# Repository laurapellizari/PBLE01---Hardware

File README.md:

# PBLE01---Hardware
Embedded hardware design for learning

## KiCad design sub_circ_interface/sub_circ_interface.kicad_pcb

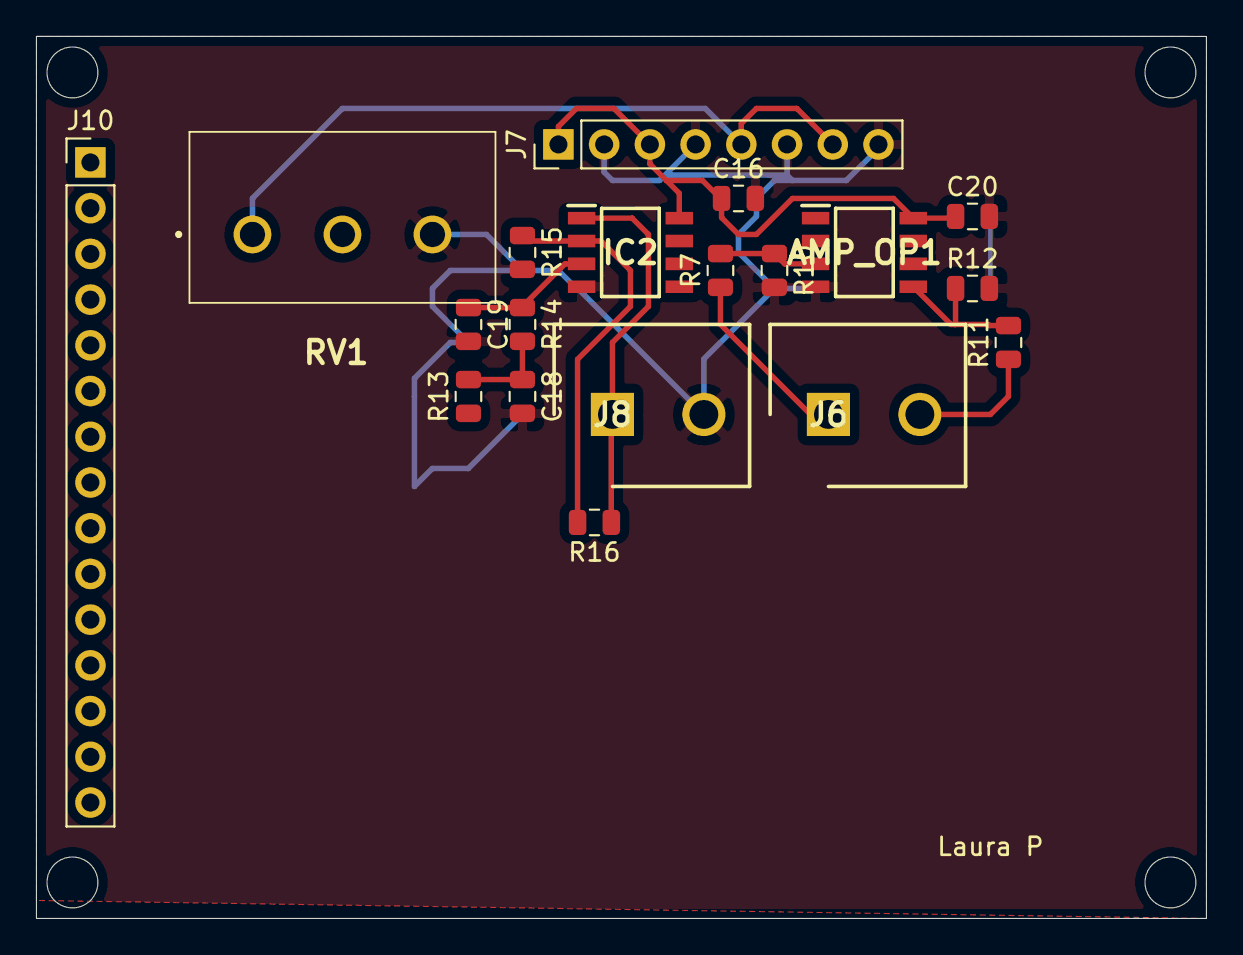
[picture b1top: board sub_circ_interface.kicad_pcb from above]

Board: 2 copper layers, 65.0 x 49.0 mm, 19 parts (0 on the bottom side), 11 nets.

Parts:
AMP_OP1: LM358DG; SOIC127P600X175-8N
C16, C20: 100nF; C_0805_2012Metric
C18, C19: 220nF; C_0805_2012Metric
IC2: LM358DG; SOIC127P600X175-8N
J6, J8: OSTTA024163; SHDR2W100P0X508_1X2_1086X900X1300P
J7: ALIM; PinHeader_1x08_P2.54mm_Vertical
J10: EXTENSÃO; PinHeader_1x15_P2.54mm_Vertical
R7, R11: 4k3; R_0805_2012Metric
R10, R12: 8k2; R_0805_2012Metric
R13: 1k; R_0805_2012Metric
R14: 3k3; R_0805_2012Metric
R15: 10k; R_0805_2012Metric
R16: 5k1; R_0805_2012Metric
RV1: POT; P160KN0QD15B10K

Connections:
+3V3: J7.5, J7.7, RV1.1
+5V: AMP_OP1.8, C16.1, C20.1, IC2.8, J7.1, J7.3
Earth: AMP_OP1.4, C16.2, C18.2, C19.2, C20.2, IC2.4, J7.2, J7.4, J7.6, J7.8, J8.2, R10.2, R12.2, R15.2, RV1.3
IN_A: AMP_OP1.3, R7.2, R10.1
IN_B: AMP_OP1.5, R11.2, R12.1
unnamed: C18.1, R13.2, R14.2
unnamed: C19.1, IC2.3, R14.1
unnamed: IC2.1, J8.1, R16.1
unnamed: IC2.2, R15.1, R16.2
unnamed: J6.1, R7.1
unnamed: J6.2, R11.1

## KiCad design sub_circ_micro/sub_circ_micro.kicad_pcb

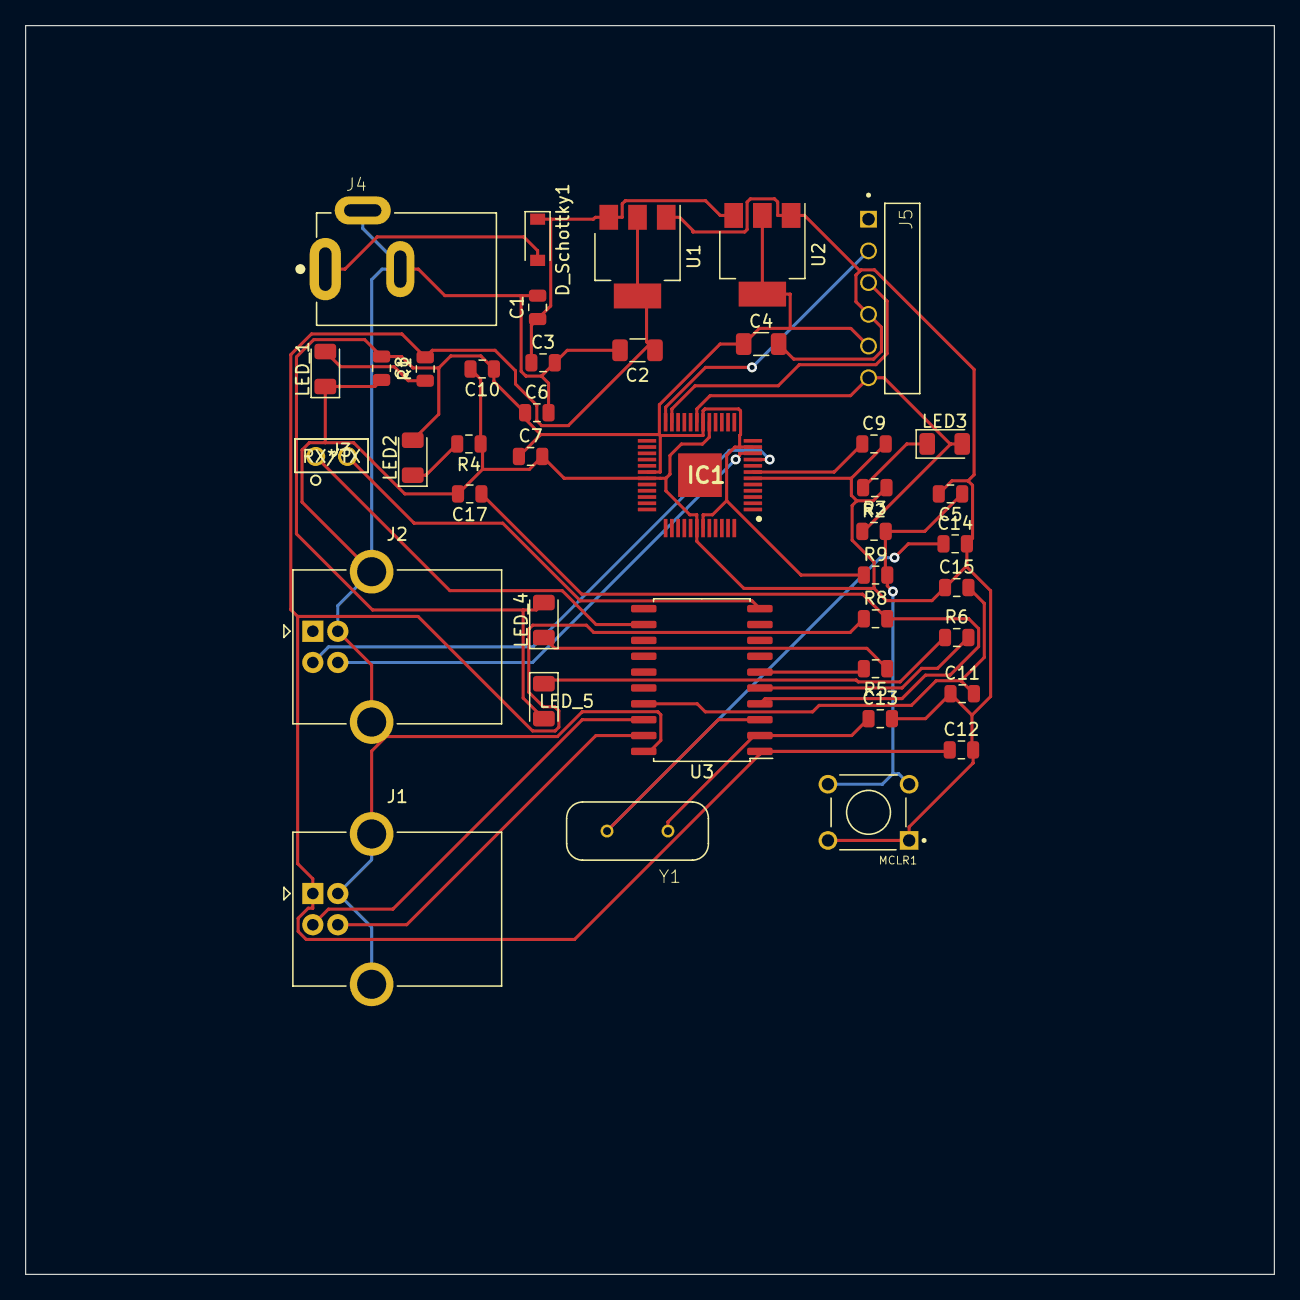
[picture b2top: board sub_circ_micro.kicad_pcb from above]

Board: 2 copper layers, 100.0 x 100.0 mm, 41 parts (0 on the bottom side), 27 nets.

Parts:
C1, C3, C5, C6, C7, C8, C10, C11, C12, C15, C17: 100nF; C_0805_2012Metric
C2, C4: 10uF; C_1206_3216Metric
C9: 10uF; C_0805_2012Metric
C13, C14: 22pF; C_0805_2012Metric
D_Schottky1: 1N5819; D_SOD-123
IC1: PIC32MM0064GPM048-I_PT; QFP50P900X900X120-49N
J1, J2: USB_B; USB_B_OST_USB-B1HSxx_Horizontal
J3: RX/TX; SSQ-102-03-T-S
J4: PJ-002A; CUI_PJ-002A
J5: ICSP; TE_826951-6
LED2: LED]; LED_1206_3216Metric
LED3: LED; LED_1206_3216Metric
LED_1: LED_ALIM; LED_1206_3216Metric
LED_4: Lx_LED; LED_1206_3216Metric
LED_5: Rx_LED; LED_1206_3216Metric
MCLR1: SWL1; SW_1825910-6-4
R1: 470; R_0805_2012Metric
R2: 1k; R_0805_2012Metric
R3, R4, R5, R6: 120; R_0805_2012Metric
R8: 4k7; R_0805_2012Metric
R9: 10k; R_0805_2012Metric
U1: LD1117S50TR_SOT223; SOT-223-3_TabPin2
U2: LD1117S33TR_SOT223; SOT-223-3_TabPin2
U3: MCP2200-I-SO; SOIC-20W_7.5x12.8mm_P1.27mm
Y1: 12MHz; XTAL_ECS-120-20-4X

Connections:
D+: J1.3, U3.19
D-: J1.2, U3.18
Earth: C1.2, C2.2, C3.2, C4.2, C5.2, C6.2, C7.2, C8.2, C9.2, C10.2, C11.1, C12.2, C13.2, C14.2, C15.1, C17.2, IC1.6, IC1.17, IC1.31, IC1.42, J1.4, J1.5, J2.4, J2.5, J4.2, J4.3, J5.4, LED_1.1, MCLR1.1, MCLR1.2, R3.1, R4.1, U1.1, U2.1, U3.20
MCLR#: IC1.19, J5.6, LED3.2, R2.1
unnamed: C5.1, MCLR1.3, MCLR1.4, R2.2, R9.2
unnamed: C11.2, C15.2, U3.17
unnamed: D_Schottky1.2, J4.1
unnamed: LED2.1, R4.2
unnamed: LED3.1, R3.2
unnamed: LED_1.2, R1.1
unnamed: LED_4.1, R5.1
unnamed: LED_5.1, R6.1
OSC1: C13.1, U3.2, Y1.1
OSC2: C14.1, U3.3, Y1.2
PGEC1: IC1.24, J5.2
PGED1: IC1.23, J5.3
RB10: IC1.9, J2.2
RB11: IC1.10, J2.3
RST: C17.1, R8.2, U3.4
RX: J3.1, U3.12
RxLED: R5.2, U3.6
TX: J3.2, U3.10
TxLED: R6.2, U3.5
VBUS: C2.1, C12.1, J1.1, R1.2, R8.1, U1.2, U3.1
VCAP: C9.1, IC1.7
VUSB3V3: C4.1, C6.1, C7.1, C8.1, C10.1, IC1.11, IC1.18, IC1.30, IC1.43, J5.5, LED2.2, LED_4.2, LED_5.2, R9.1, U2.2
Vin: C1.1, C3.1, D_Schottky1.1, U1.3, U2.3

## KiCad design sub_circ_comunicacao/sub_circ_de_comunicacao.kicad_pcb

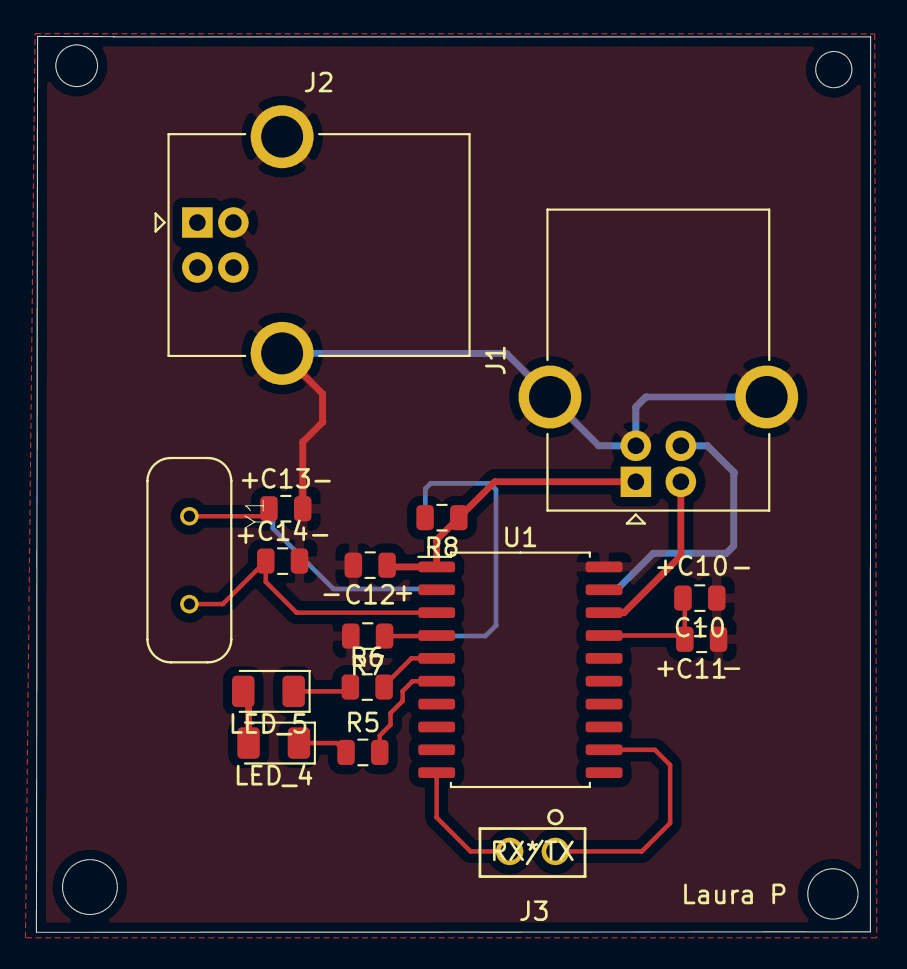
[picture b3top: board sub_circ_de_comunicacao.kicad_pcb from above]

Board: 2 copper layers, 46.3 x 49.8 mm, 16 parts (0 on the bottom side), 15 nets.

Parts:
C10, C11, C12: 100nF; C_0805_2012Metric
C13, C14: 22pF; C_0805_2012Metric
J1, J2: USB_B; USB_B_OST_USB-B1HSxx_Horizontal
J3: RX/TX; SSQ-102-03-T-S
LED_4: Lx_LED; LED_1206_3216Metric
LED_5: Rx_LED; LED_1206_3216Metric
R5, R6: 120; R_0805_2012Metric
R7: 10k; R_0805_2012Metric
R8: 4k7; R_0805_2012Metric
U1: MCP2200-I-SO; SOIC-20W_7.5x12.8mm_P1.27mm
Y1: 12MHz; XTAL_ECS-120-20-4X

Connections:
+3V3: LED_4.2, LED_5.2
D+: J1.3, U1.19
D-: J1.2, U1.18
Earth: C10.1, C11.1, C12.2, C13.2, C14.2, J1.4, J1.5, J2.4, J2.5, R7.2, U1.20
unnamed: C10.2, C11.2, U1.17
unnamed: LED_4.1, R5.1
unnamed: LED_5.1, R6.1
OSC1: C13.1, U1.2, Y1.1
OSC2: C14.1, U1.3, Y1.2
RST: R7.1, R8.2, U1.4
RX: J3.1, U1.12
RxLED: R5.2, U1.6
TX: J3.2, U1.10
TxLED: R6.2, U1.5
VBUS: C12.1, J1.1, R8.1, U1.1

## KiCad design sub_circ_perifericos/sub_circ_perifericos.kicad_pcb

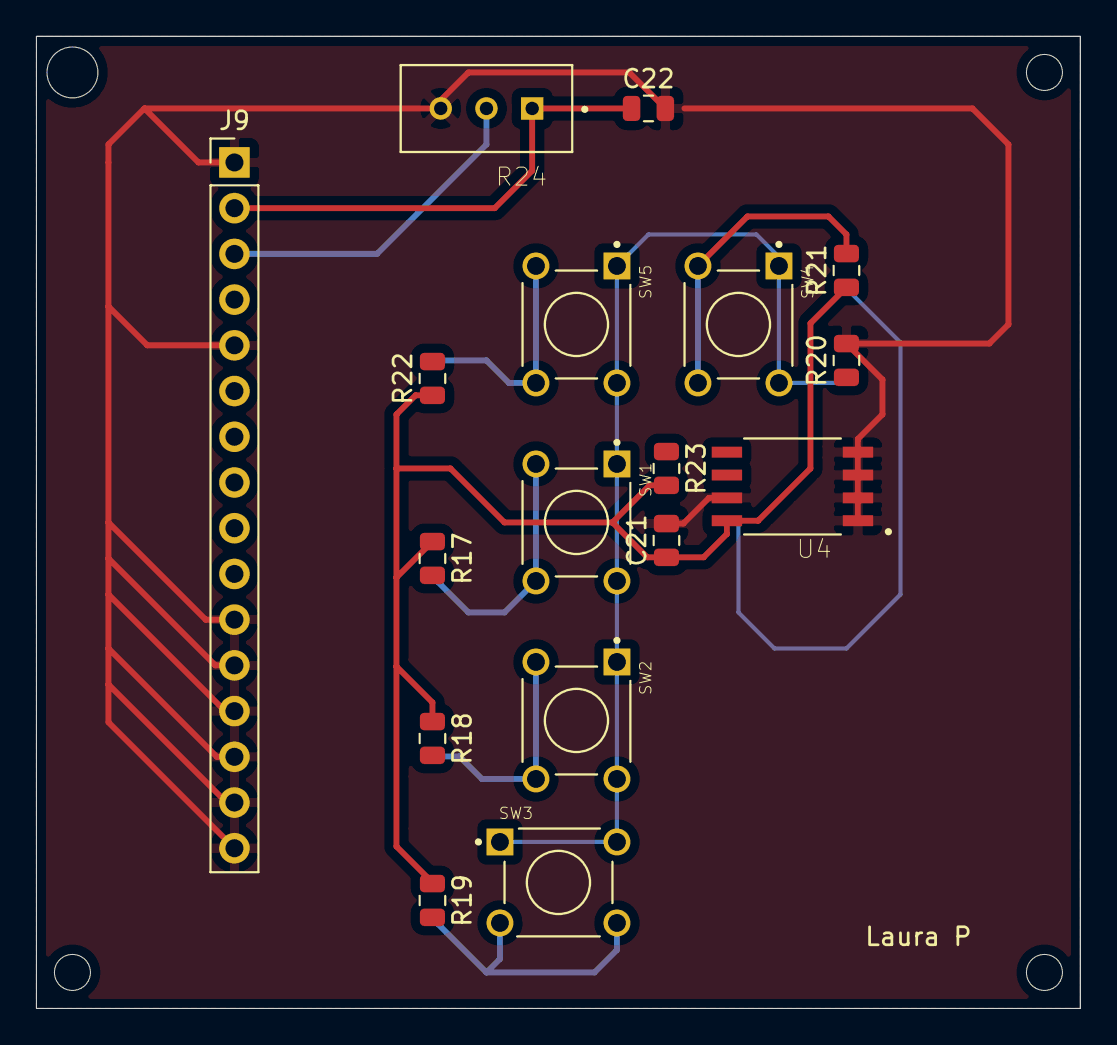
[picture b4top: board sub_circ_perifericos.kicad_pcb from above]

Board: 2 copper layers, 58.0 x 54.0 mm, 17 parts (0 on the bottom side), 11 nets.

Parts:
C21, C22: 100nF; C_0805_2012Metric
J9: LDC_header; PinHeader_1x16_P2.54mm_Vertical
R17: 8k2; R_0805_2012Metric
R18: 6k2; R_0805_2012Metric
R19: 4k7; R_0805_2012Metric
R20: 10k; R_0805_2012Metric
R21: 3k3; R_0805_2012Metric
R22: 1k; R_0805_2012Metric
R23: 2k; R_0805_2012Metric
R24: POT_LCD; TRIM_3296W-1-103RLF
SW1, SW2, SW3, SW4, SW5: 1825910-6; SW_1825910-6-4
U4: 24LC512-I_SM; SOIC127P794X202-8N

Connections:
+3V3: C21.1, R17.1, R18.1, R19.1, R21.1, R22.1, R23.2, U4.8
+5V: C22.1, J9.2, R24.1
Earth: C21.2, C22.2, J9.1, J9.5, J9.11, J9.12, J9.13, J9.14, J9.15, J9.16, R20.2, R24.3, U4.1, U4.2, U4.3, U4.4, U4.7
unnamed: J9.3, R24.2
unnamed: R17.2, SW1.3, SW1.4
unnamed: R18.2, SW2.3, SW2.4
unnamed: R19.2, SW3.3, SW3.4
unnamed: R21.2, SW4.3, SW4.4
unnamed: R22.2, SW5.3, SW5.4
SDA: R23.1, U4.5
TECLADO: R20.1, SW1.1, SW1.2, SW2.1, SW2.2, SW3.1, SW3.2, SW4.1, SW4.2, SW5.1, SW5.2

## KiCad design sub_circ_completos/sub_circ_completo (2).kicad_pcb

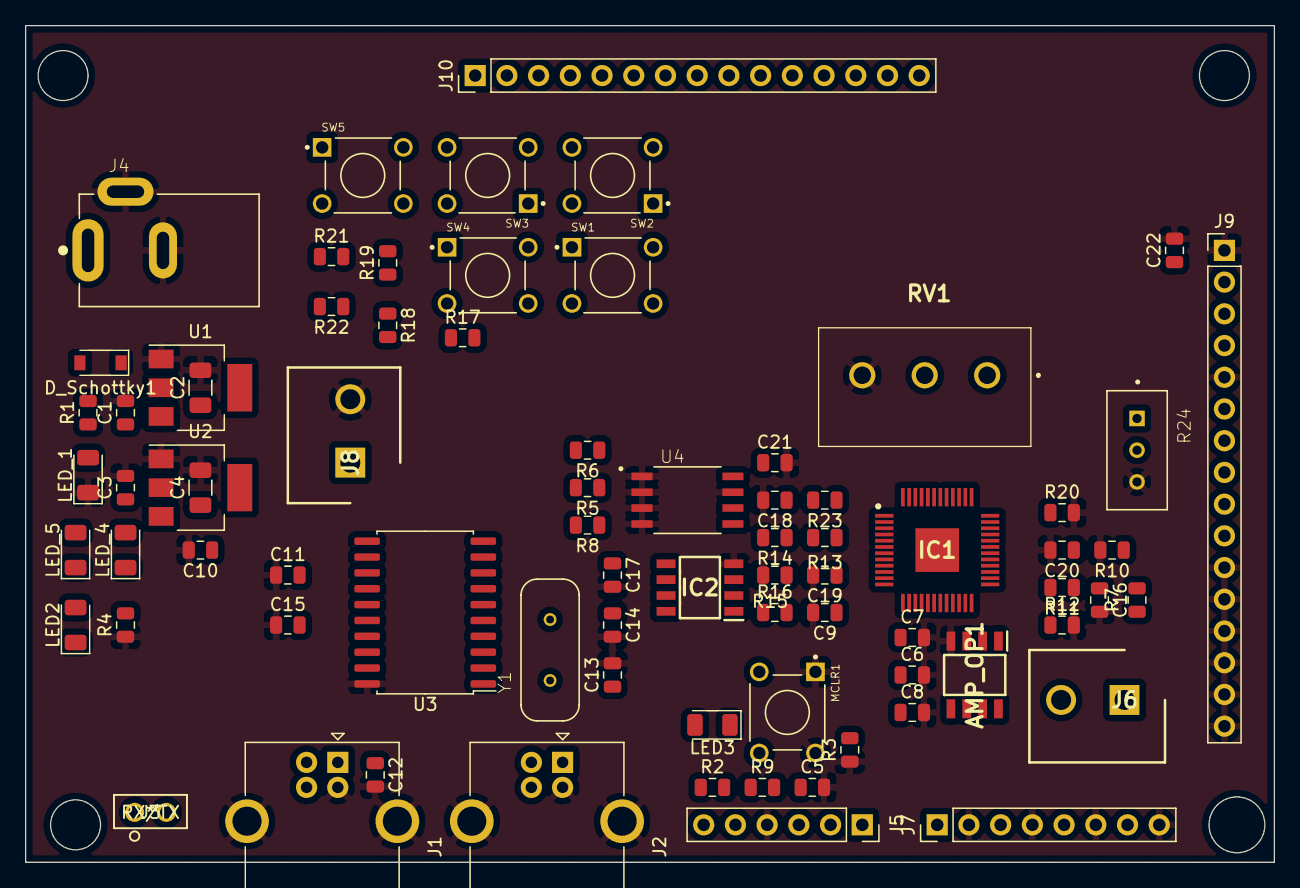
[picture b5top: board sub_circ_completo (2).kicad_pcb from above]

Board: 2 copper layers, 100.0 x 67.0 mm, 77 parts (0 on the bottom side), 69 nets, no tracks yet.

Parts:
AMP_OP1: LM358DG; SOIC127P600X175-8N
C1, C3, C5, C6, C7, C8, C10, C11, C12, C15, C16, C17, C20, C21, C22: 100nF; C_0805_2012Metric
C2, C4: 10uF; C_1206_3216Metric
C9: 10uF; C_0805_2012Metric
C13, C14: 22pF; C_0805_2012Metric
C18, C19: 220nF; C_0805_2012Metric
D_Schottky1: 1N5819; D_SOD-123
IC1: PIC32MM0064GPM048-I_PT; QFP50P900X900X120-49N
IC2: LM358DG; SOIC127P600X175-8N
J1, J2: USB_B; USB_B_OST_USB-B1HSxx_Horizontal
J3: RX/TX; SSQ-102-03-T-S
J4: PJ-002A; CUI_PJ-002A
J5: ICSP; PinSocket_1x06_P2.54mm_Vertical
J6, J8: OSTTA024163; SHDR2W100P0X508_1X2_1086X900X1300P
J7: ALIM; PinHeader_1x08_P2.54mm_Vertical
J9: LDC_header; PinHeader_1x16_P2.54mm_Vertical
J10: EXTENSÃO; PinHeader_1x15_P2.54mm_Vertical
LED2, LED3: LED; LED_1206_3216Metric
LED_1: LED_ALIM; LED_1206_3216Metric
LED_4: Lx_LED; LED_1206_3216Metric
LED_5: Rx_LED; LED_1206_3216Metric
MCLR1: SWL1; SW_1825910-6-4
R1: 470; R_0805_2012Metric
R2, R13, R22: 1k; R_0805_2012Metric
R3, R4, R5, R6: 120; R_0805_2012Metric
R7, R11: 4k3; R_0805_2012Metric
R8, R19: 4k7; R_0805_2012Metric
R9, R15, R20: 10k; R_0805_2012Metric
R10, R12, R17: 8k2; R_0805_2012Metric
R14, R21: 3k3; R_0805_2012Metric
R16: 5k1; R_0805_2012Metric
R18: 6k2; R_0805_2012Metric
R23: 2k; R_0805_2012Metric
R24: POT_LCD; TRIM_3296W-1-103RLF
RV1: POT; P160KN0QD15B10K
SW1, SW2, SW3, SW4, SW5: 1825910-6; SW_1825910-6-4
U1: LD1117S50TR_SOT223; SOT-223-3_TabPin2
U2: LD1117S33TR_SOT223; SOT-223-3_TabPin2
U3: MCP2200-I-SO; SOIC-20W_7.5x12.8mm_P1.27mm
U4: 24LC512-I_SM; SOIC127P794X202-8N
Y1: 12MHz; XTAL_ECS-120-20-4X

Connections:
AN4: AMP_OP1.7, IC1.25
AN11: AMP_OP1.1, IC1.26
D4: IC1.35, J9.7
D5: IC1.34, J9.8
D6: IC1.33, J9.9
D7: IC1.32, J9.10
D+: J1.3, U3.19
D-: J1.2, U3.18
E: IC1.28, J9.6
Earth: AMP_OP1.4, C1.2, C2.2, C3.2, C4.2, C5.2, C6.2, C7.2, C8.2, C9.2, C10.2, C11.1, C12.2, C13.2, C14.2, C15.1, C16.2, C17.2, C18.2, C19.2, C20.2, C21.2, C22.2, IC1.6, IC1.17, IC1.31, IC1.42, IC2.4, J1.4, J1.5, J2.4, J2.5, J4.2, J4.3, J5.4, J7.2, J7.4, J7.6, J7.8, J8.2, J9.1, J9.5, J9.11, J9.12, J9.13, J9.14, J9.15, J9.16, LED_1.1, MCLR1.1, MCLR1.2, R3.1, R4.1, R10.2, R12.2, R15.2, R20.2, R24.3, RV1.3, U1.1, U2.1, U3.20, U4.1, U4.2, U4.3, U4.4, U4.7
IN_A: AMP_OP1.3, R7.2, R10.1
IN_B: AMP_OP1.5, R11.2, R12.1
MCLR#: IC1.19, J5.6, LED3.2, R2.1
unnamed: C5.1, MCLR1.3, MCLR1.4, R2.2, R9.2
unnamed: C11.2, C15.2, U3.17
unnamed: C18.1, R13.2, R14.2
unnamed: C19.1, IC2.3, R14.1
unnamed: D_Schottky1.2, J4.1
unnamed: IC2.1, J8.1, R16.1
unnamed: IC2.2, R15.1, R16.2
unnamed: J6.1, R7.1
unnamed: J6.2, R11.1
unnamed: J9.3, R24.2
unnamed: LED2.1, R4.2
unnamed: LED3.1, R3.2
unnamed: LED_1.2, R1.1
unnamed: LED_4.1, R5.1
unnamed: LED_5.1, R6.1
unnamed: R17.2, SW1.3, SW1.4
unnamed: R18.2, SW2.3, SW2.4
unnamed: R19.2, SW3.3, SW3.4
unnamed: R21.2, SW4.3, SW4.4
unnamed: R22.2, SW5.3, SW5.4
OSC1: C13.1, U3.2, Y1.1
OSC2: C14.1, U3.3, Y1.2
PGEC1: IC1.24, J5.2
PGED1: IC1.23, J5.3
PIN_2: IC1.2, J10.1
PIN_3: IC1.3, J10.2
PIN_8: IC1.8, J10.3
PIN_13: IC1.13, J10.4
PIN_14: IC1.14, J10.5
PIN_15: IC1.15, J10.6
PIN_16: IC1.16, J10.7
PIN_21: IC1.21, J10.8
PIN_22: IC1.22, J10.9
PIN_36: IC1.36, J10.10
PIN_39: IC1.39, J10.11
PIN_40: IC1.40, J10.12
PIN_41: IC1.41, J10.13
PIN_45: IC1.45, J10.14
PIN_48: IC1.48, J10.15
POT: IC1.27, RV1.2
PWM: IC1.1, R13.1
RB10: IC1.9, J2.2
RB11: IC1.10, J2.3
RS: IC1.29, J9.4
RST: C17.1, IC1.38, R8.2, U3.4
RX: IC1.20, J3.1, U3.12
RxLED: R5.2, U3.6
SCL: IC1.12, U4.6
SDA: IC1.47, R23.1, U4.5
TECLADO: IC1.4, R20.1, SW1.1, SW1.2, SW2.1, SW2.2, SW3.1, SW3.2, SW4.1, SW4.2, SW5.1, SW5.2
TX: IC1.44, J3.2, U3.10
TxLED: R6.2, U3.5
VBUS: AMP_OP1.8, C2.1, C12.1, C16.1, C20.1, C22.1, IC2.8, J1.1, J7.1, J7.3, J9.2, R1.2, R8.1, R24.1, U1.2, U3.1
VCAP: C9.1, IC1.7
VUSB3V3: C4.1, C6.1, C7.1, C8.1, C10.1, C21.1, IC1.11, IC1.18, IC1.30, IC1.43, J5.5, J7.5, J7.7, LED2.2, LED_4.2, LED_5.2, R9.1, R17.1, R18.1, R19.1, R21.1, R22.1, R23.2, RV1.1, U2.2, U4.8
Vin: C1.1, C3.1, D_Schottky1.1, U1.3, U2.3

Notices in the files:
parts and their libraries:
Copyright 2016 Accelerated Designs. All rights reserved.
